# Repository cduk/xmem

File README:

This is my first attempt at designing a PCB.

It is an expansion board for the Arduino ATmega to have an external SRAM chip.

I'm using the AS6C1008 128K x 8 bit chip as I happened to have several of these on hand. You can either use half of it, which is as much as the ATmega can address without banking, or you can bank switch using the A15 pin.

As this is only a 55ns ram chip, maximum clock speed should be ~18MHz without waitstates. I still need to test the board and chips to see how fast the RAM chips can actually be driven.

This PCB was designed from scratch by myself as a way to learn to use KiCad: http://kicad.org/

I have seen several other designs already including most notably:

http://andybrown.me.uk/2011/08/28/512kb-sram-expansion-for-the-arduino-mega-design/

Which I'm sure both influenced my own design both consciously and probably sub-consciously and so I want to make sure I credit Andy for this work.

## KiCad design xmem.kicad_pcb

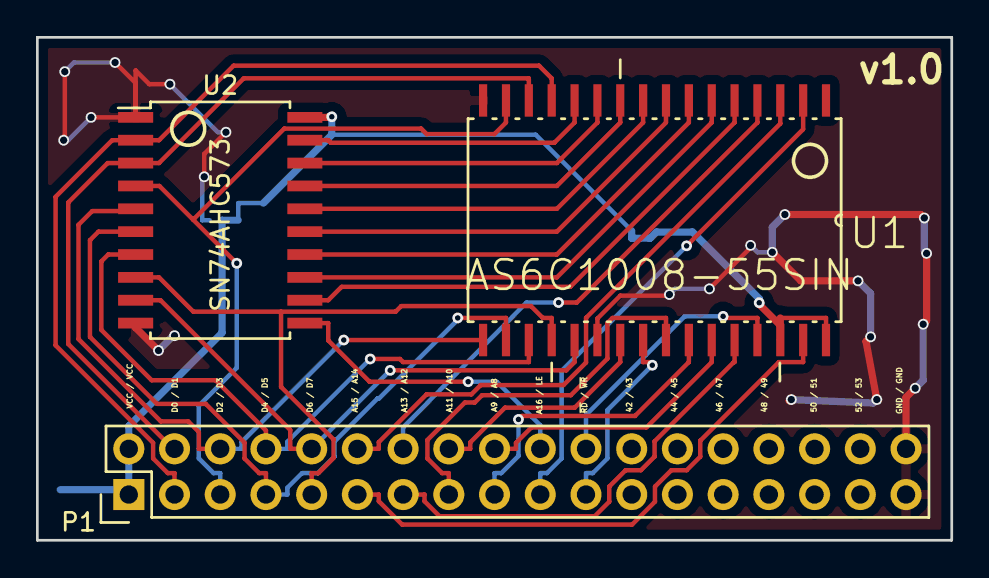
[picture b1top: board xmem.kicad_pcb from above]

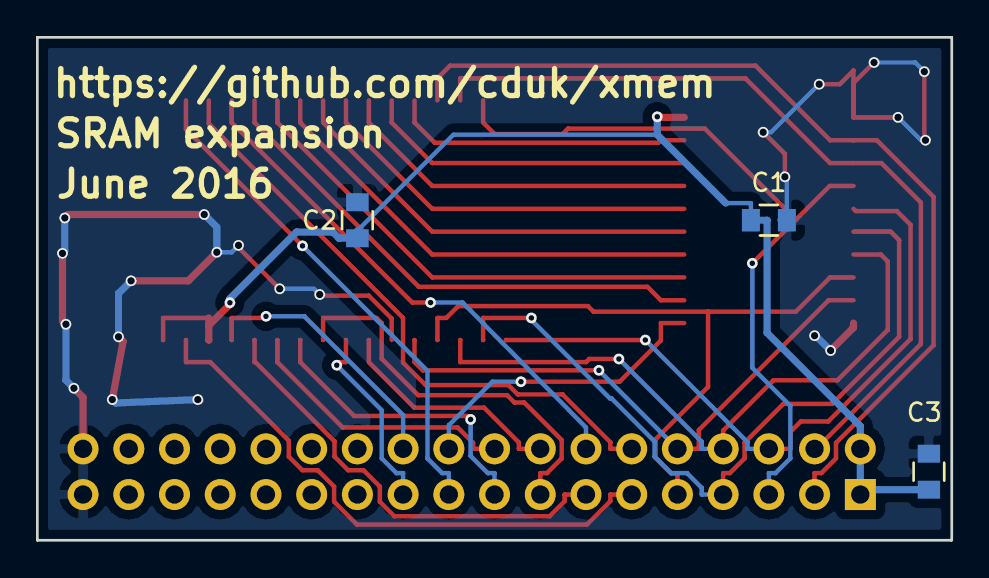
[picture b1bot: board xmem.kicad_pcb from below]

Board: 2 copper layers, 50.8 x 27.9 mm, 6 parts (3 on the bottom side), 30 nets.

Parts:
C1, C2, C3: C; C_0805
P1: CONN_02X18; Pin_Header_Straight_2x18
U1: AS6C1008-55SIN; SOIC127P1407X299-32N
U2: SN74AHC573; SOIC-20_7.5x12.8mm_Pitch1.27mm

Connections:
/A0: U1.12, U2.19
/A1: U1.11, U2.18
/A2: U1.10, U2.17
/A3: U1.9, U2.16
/A4: U1.8, U2.15
/A5: U1.7, U2.14
/A6: U1.6, U2.13
/A7: U1.5, U2.12
/A8: P1.18, U1.27
/A9: P1.17, U1.26
/A10: P1.16, U1.23
/A11: P1.15, U1.25
/A12: P1.14, U1.4
/A13: P1.13, U1.28
/A14: P1.12, U1.3
/A15: P1.11, U1.31
/A16: P1.19, U1.2
/D0: P1.3, U1.13, U2.2
/D1: P1.4, U1.14, U2.3
/D2: P1.5, U1.15, U2.4
/D3: P1.6, U1.17, U2.5
/D4: P1.7, U1.18, U2.6
/D5: P1.8, U1.19, U2.7
/D6: P1.9, U1.20, U2.8
/D7: P1.10, U1.21, U2.9
/LE: P1.20, U2.11
/~RD: P1.21, U1.24
/~WR: P1.22, U1.29
GND: C1.2, C2.2, C3.2, P1.35, P1.36, U1.16, U1.22, U2.1, U2.10
VCC: C1.1, C2.1, C3.1, P1.1, P1.2, U1.30, U1.32, U2.20

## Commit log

2016-06-13 Add readme
2016-06-14 Update to connect remaining pins and update footprints
2016-06-14 Add flood fill ground plane. Fix close tracks. Add text
2016-06-14 RC1 - WIP
2016-06-15 Add stitching vias
2016-06-15 Add pin labels
2021-11-09 Update README
    https://forum.kicad.info/t/warning-avoid-all-links-to-kicad-pcb-org-use-kicad-org/31521
